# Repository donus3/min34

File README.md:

# min34

A minimal split keyboard with 34 keys

## Features
 - 34 keys (inspired by Sweep)
 - Support a hotswap switch both MX and Kailh low profile style (inspired by SofleKeyboard)
 - Using seeed studio XIAO series microcontroller which means both wire and wireless are available
 - Support a battery switch on/off if Bluetooth microcontroller is used
 - The PCB is reversible
 - No reset button (it's already on the microcontroller)

I don't focus on adding more features like an OLED display or a rotary encoder because I would like to keep it as simple as possible and I personally
don't use them in my daily life (as a programmer).

## Compnents
 - 2x PCBs (for left and right)
 - 2x seeed studio XIAO compatible boards.
 - 34 switches of MX or Kailh low profile style
 - 34 kailh switch sockets (MX or Kailh low profile)
 - 34 diodes 1N4148W
 - 34 keycaps
 - (optional; only for battery support) 2x power switches (MSK 12C02)
 - (optional; only for wire support) 2x TRRS connectors
 - (optional; only for wire support) 1x TRRS cable
 - 1 USB Cable

## Firmware
Please refer to [min34 zmk config](./firmware)

## Thanks to
 - [SofleKeyboard](https://github.com/josefadamcik/SofleKeyboard)
 - [crkbd](https://github.com/foostan/crkbd)
 - [Slice36](https://github.com/MReavley/Slice36)
 - [Sweep](https://github.com/davidphilipbarr/Sweep)
 - Seeed xiao nrf52840 mcu: https://www.seeedstudio.com/Seeed-XIAO-BLE-nRF52840-p-5201.html
 - Seeed Fusion PCBA service: https://www.seeedstudio.com/pcb-assembly.html
 - Seeed Fusion DIY Mechanical Keyboard contest: https://www.seeedstudio.com/seeed-fusion-diy-xiao-mechanical-keyboard-contest.html

## Gallery

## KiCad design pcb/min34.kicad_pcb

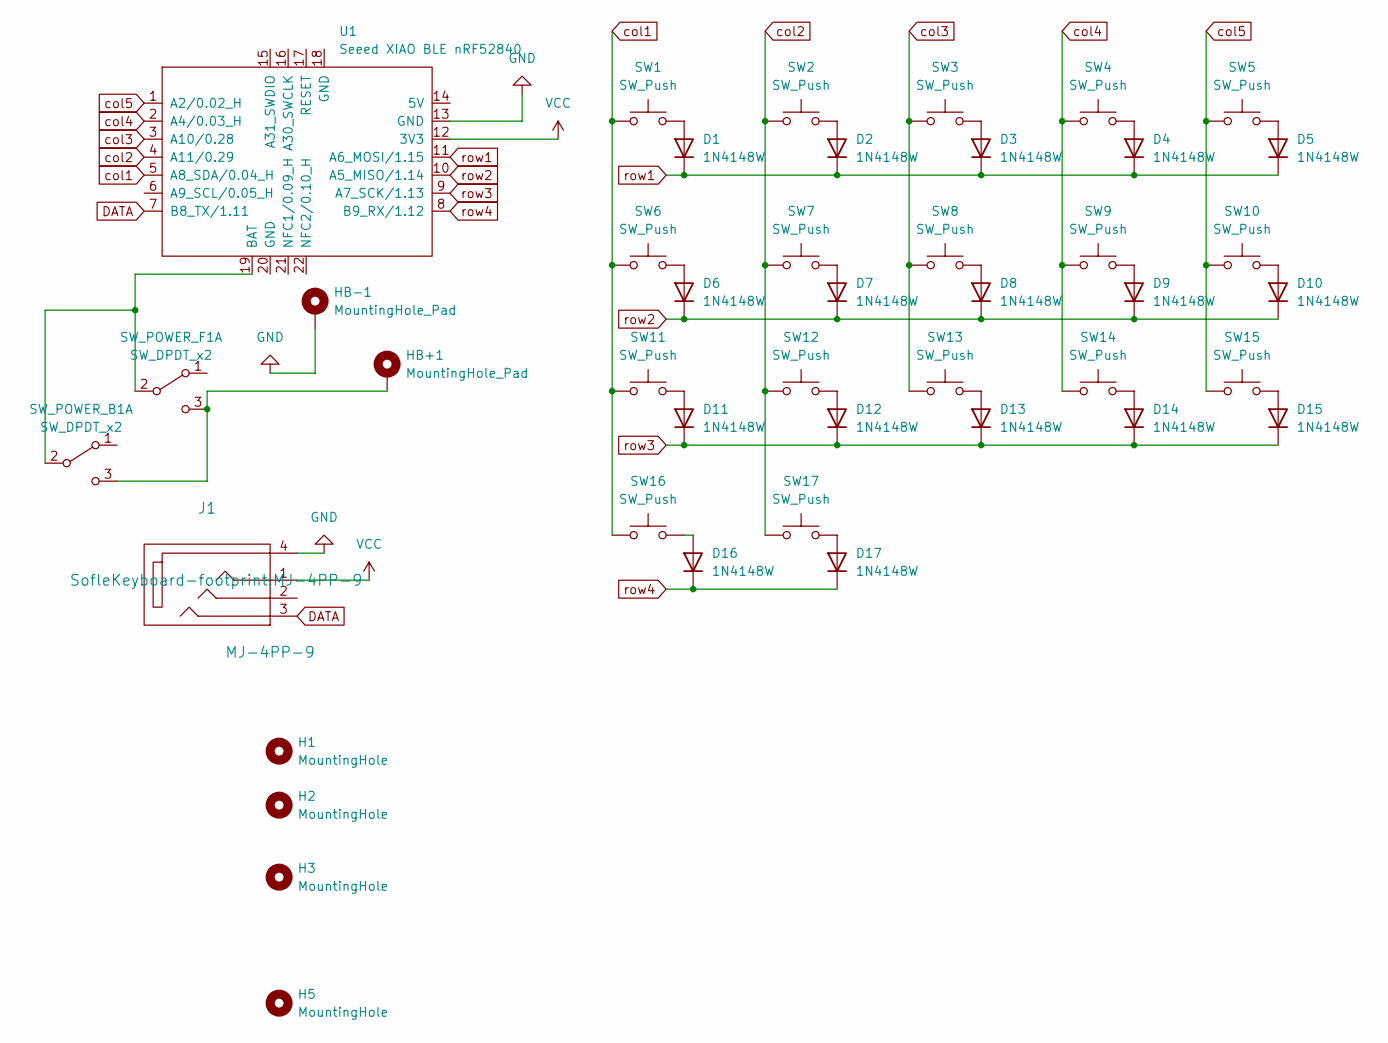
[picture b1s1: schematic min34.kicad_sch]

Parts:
D1, D2, D3, D4, D5, D6, D7, D8, D9, D10, D11, D12, D13, D14, D15, D16, D17: 1N4148W; Diode_SOD123
H1, H2, H3, H5: MountingHole; HOLE_M2_TH
HB+1: MountingHole_Pad; 1pin_conn
HB-1: MountingHole_Pad; 1pin_conn
J1: MJ-4PP-9
SW1, SW2, SW3, SW4, SW5, SW6, SW7, SW8, SW9, SW10, SW11, SW12, SW13, SW14, SW15, SW16, SW17: SW_Push; CherryMX_KailhLowProfile_Hotswap
SW_POWER_B1: SW_DPDT_x2; SPDT_C128955
SW_POWER_F1: SW_DPDT_x2; SPDT_C128955
U1: Seeed XIAO BLE nRF52840; xiao-ble-tht

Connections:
DATA: J1.3, U1.7 (B8_TX/1.11)
GND: HB-1.1, J1.4, U1.13 (GND); also elsewhere on the board
unnamed: D1.2 (A), SW1.2
unnamed: D2.2 (A), SW2.2
unnamed: D3.2 (A), SW3.2
unnamed: D4.2 (A), SW4.2
unnamed: D5.2 (A), SW5.2
unnamed: D6.2 (A), SW6.2
unnamed: D7.2 (A), SW7.2
unnamed: D8.2 (A), SW8.2
unnamed: D9.2 (A), SW9.2
unnamed: D10.2 (A), SW10.2
unnamed: D11.2 (A), SW11.2
unnamed: D12.2 (A), SW12.2
unnamed: D13.2 (A), SW13.2
unnamed: D14.2 (A), SW14.2
unnamed: D15.2 (A), SW15.2
unnamed: D16.2 (A), SW16.2
unnamed: D17.2 (A), SW17.2
unnamed 19: HB+1.1, SW_POWER_B1.3 (C), SW_POWER_F1.3 (C); also elsewhere on the board
unnamed: SW_POWER_B1.2 (B), SW_POWER_F1.2 (B), U1.19 (BAT)
VCC: J1.1, U1.12 (3V3)
col1: SW1.1, SW6.1, SW11.1, SW16.1, U1.5 (A8_SDA/0.04_H)
col2: SW2.1, SW7.1, SW12.1, SW17.1, U1.4 (A11/0.29)
col3: SW3.1, SW8.1, SW13.1, U1.3 (A10/0.28)
col4: SW4.1, SW9.1, SW14.1, U1.2 (A4/0.03_H)
col5: SW5.1, SW10.1, SW15.1, U1.1 (A2/0.02_H)
row1: D1.1 (K), D2.1 (K), D3.1 (K), D4.1 (K), D5.1 (K), U1.11 (A6_MOSI/1.15)
row2: D6.1 (K), D7.1 (K), D8.1 (K), D9.1 (K), D10.1 (K), U1.10 (A5_MISO/1.14)
row3: D11.1 (K), D12.1 (K), D13.1 (K), D14.1 (K), D15.1 (K), U1.9 (A7_SCK/1.13)
row4: D16.1 (K), D17.1 (K), U1.8 (B9_RX/1.12)

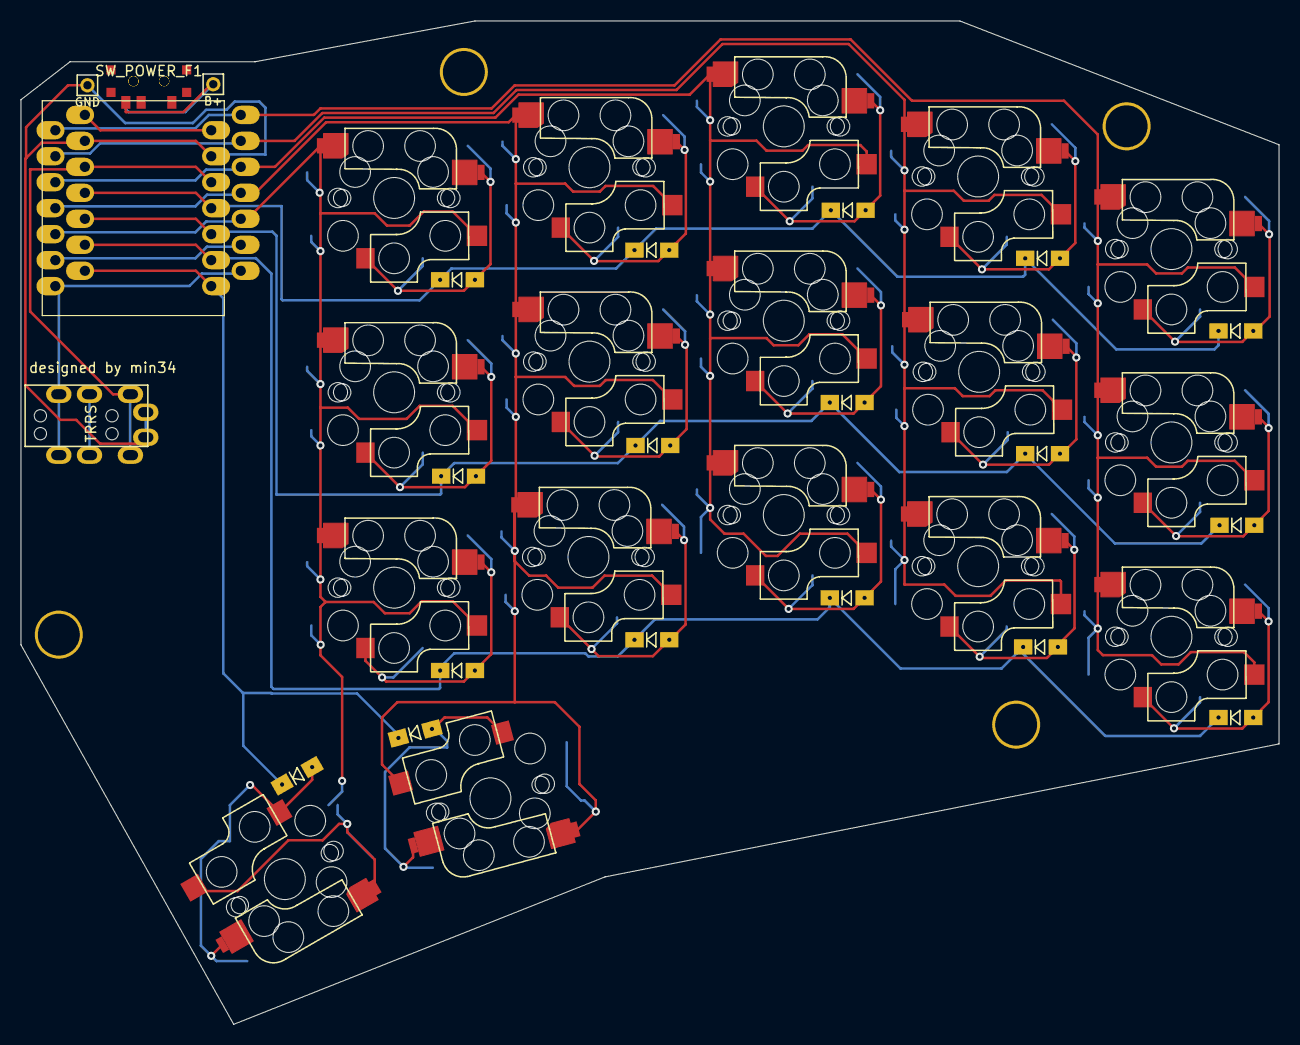
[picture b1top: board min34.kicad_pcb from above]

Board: 2 copper layers, 123.0 x 98.1 mm, 44 parts (0 on the bottom side), 31 nets.

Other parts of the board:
B+: MountingHole_Pad; 1pin_conn
GND: MountingHole_Pad; 1pin_conn

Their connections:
GND: GND.1; also elsewhere on the board
unnamed 19: B+.1; also elsewhere on the board

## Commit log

2022-10-14 min34 day 1
2022-10-17 thanks to seeed studio
2022-10-30 update plate 3d model
2022-10-30 update case 3d model
2022-11-01 update plate 3d model with screw
2022-12-03 3d-print: case support hole
2022-12-03 readme: update images
